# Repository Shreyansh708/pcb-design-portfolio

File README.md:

# PCB Design Portfolio

Electronics PCB design projects developed using KiCad, covering schematic capture, PCB layout, routing, design verification, and manufacturing outputs.

---

## 01 — Single LED PCB

**Status:** Completed  
**EDA Tool:** KiCad 10.0.5  
**Board Type:** 2-layer PCB  
**Board Dimensions:** 25.05 mm × 44.05 mm  
**Board Thickness:** 1.6 mm
### PCB Layout

### Schematic

### Overview

A compact single-LED PCB designed through the complete PCB development workflow, from schematic capture to PCB layout and manufacturing-output generation.

### Design Workflow

- Schematic capture
- Component placement
- PCB layout and routing
- Board outline definition
- Design-rule verification
- Gerber generation
- PTH and NPTH drill-file generation

### Project Files

The repository contains:

- KiCad project file (`.kicad_pro`)
- KiCad schematic (`.kicad_sch`)
- KiCad PCB layout (`.kicad_pcb`)
- Gerber manufacturing files
- PTH and NPTH drill files
- Gerber job file

### Tools

**KiCad 10.0.5**

---

## 02 — AstraDrive BLDC/PMSM Controller

**Status:** Work in Progress  
**EDA Tool:** KiCad  
**Controller:** STM32G474RE  
**System:** 48 V 3-phase BLDC/PMSM motor controller

### Overview

A hardware development project for a 48 V 3-phase BLDC/PMSM motor controller, designed around an STM32G4 microcontroller and intended for applications such as robotics, AGVs, drones, and electric mobility.

The project is being developed as a hierarchical KiCad design with dedicated functional subsystems.

### Current Architecture

The design currently includes:

- STM32G474RE control subsystem
- 3-phase MOSFET bridge
- Gate-driver subsystem
- Current sensing
- Hall-sensor feedback
- Encoder interface
- DC-bus voltage sensing
- Temperature monitoring
- CAN-FD interface
- Display/UI interface
- Programming/debug interface

### Development Status

The system architecture and hierarchical schematic are currently under development. PCB component placement and routing are the next stages of development.

## About

Electrical & Electronics Engineering undergraduate interested in:

- Embedded Systems
- ARM Microcontrollers
- PCB Design
- IoT
- Motor Control
- Digital Electronics
- Hardware Development
- Low-level Firmware
- ---

## 03 — Heart-Shaped Decorative LED PCB

**Status:** Work in Progress — PCB Routing  
**EDA Tool:** KiCad 10.0  
**Board:** 2-layer PCB  
**Thickness:** 1.6 mm

### Overview

A custom heart-shaped LED PCB currently under development. The project explores custom board geometry, component placement, and PCB routing using KiCad.

### Current Development

- Custom heart-shaped board outline
- Component placement
- PCB routing in progress
- Design-rule verification to follow

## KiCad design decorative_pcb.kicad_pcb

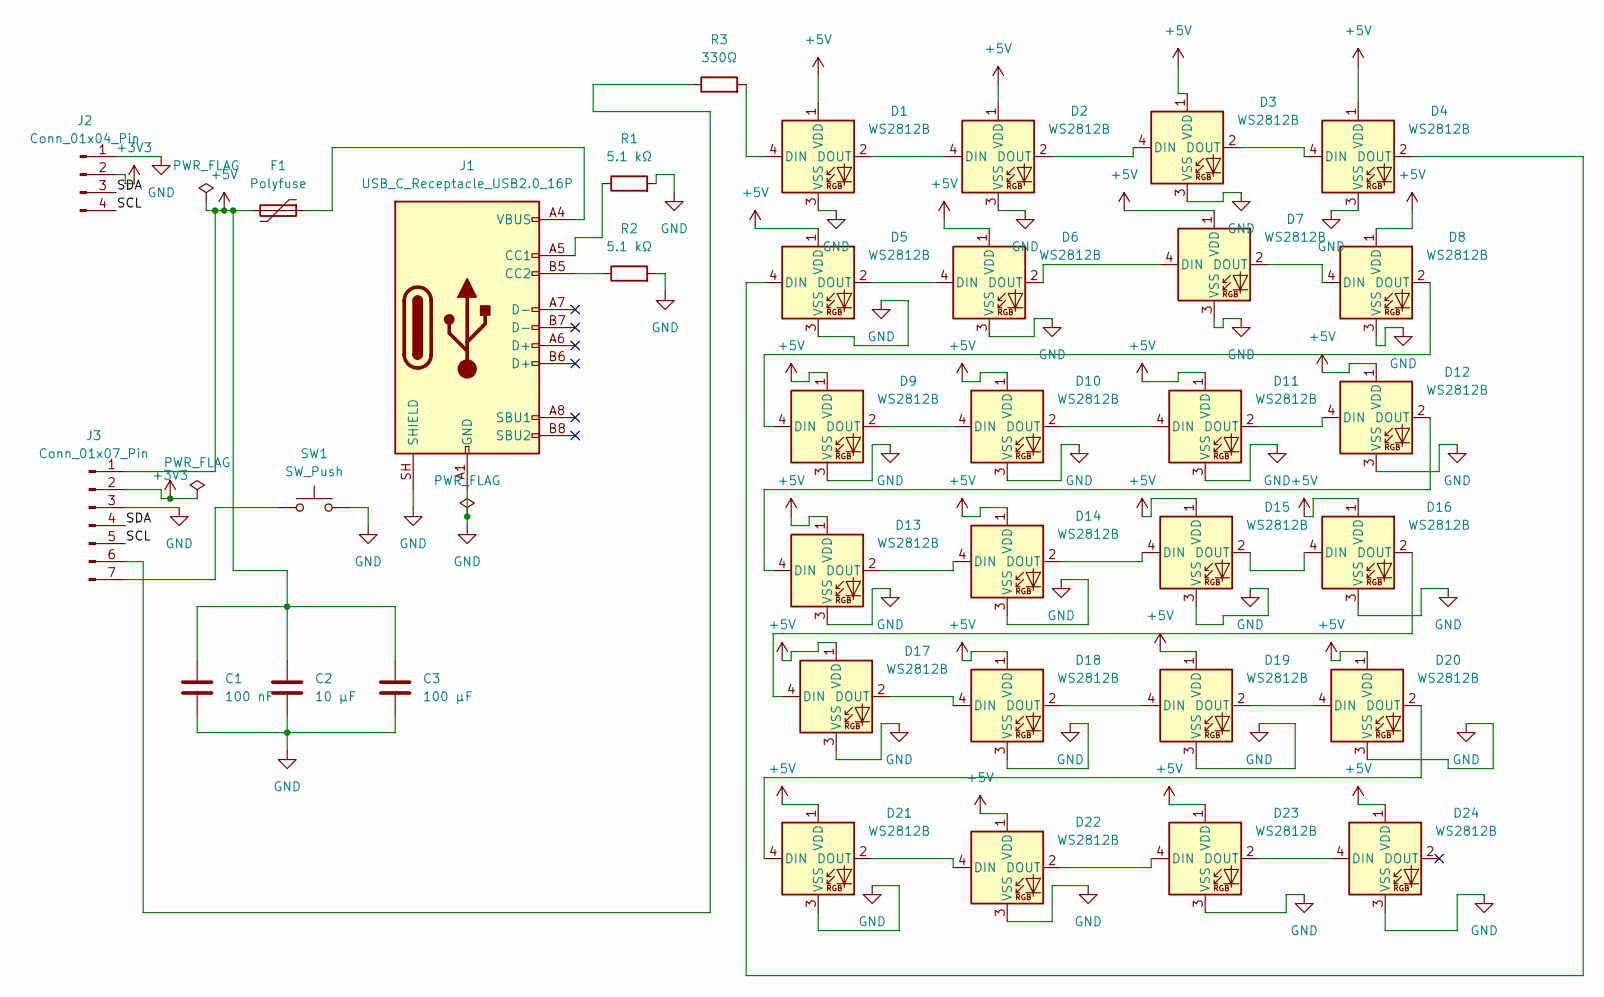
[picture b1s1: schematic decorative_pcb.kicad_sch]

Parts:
C1: 100 nF; C_0805_2012Metric
C2: 10 µF; C_0805_2012Metric
C3: 100 µF; C_Radial_D5.0mm_H5.0mm_P2.00mm
D1, D2, D3, D4, D5, D6, D7, D8, D9, D10, D11, D12, D13, D14, D15, D16, D17, D18, D19, D20, D21, D22, D23, D24: WS2812B; LED_WS2812B_PLCC4_5.0x5.0mm_P3.2mm
F1: Polyfuse; Fuse_Bourns_MF-RG300
J1: USB_C_Receptacle_USB2.0_16P; USB_C_Receptacle_GCT_USB4105-xx-A_16P_TopMnt_Horizontal
J2: Conn_01x04_Pin; FanPinHeader_1x04_P2.54mm_Vertical
J3: Conn_01x07_Pin; PinHeader_1x07_P2.54mm_Vertical
R1, R2: 5.1 kΩ; R_0805_2012Metric
R3: 330Ω; R_0805_2012Metric
SW1: SW_Push; SW_PUSH_6mm

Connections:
+3V3: J2.2, J3.2
+5V: C1.1, C2.1, C3.1, D1.1 (VDD), D2.1 (VDD), D3.1 (VDD), D4.1 (VDD), D5.1 (VDD), D6.1 (VDD), D7.1 (VDD), D8.1 (VDD), D9.1 (VDD), D10.1 (VDD), D11.1 (VDD), D12.1 (VDD), D13.1 (VDD), D14.1 (VDD), D15.1 (VDD), D16.1 (VDD), D17.1 (VDD), D18.1 (VDD), D19.1 (VDD), D20.1 (VDD), D21.1 (VDD), D22.1 (VDD), D23.1 (VDD), D24.1 (VDD), F1.2, J3.1
/SCL: J2.4, J3.5
/SDA: J2.3, J3.4
GND: C1.2, C2.2, C3.2, D1.3 (VSS), D2.3 (VSS), D3.3 (VSS), D4.3 (VSS), D5.3 (VSS), D6.3 (VSS), D7.3 (VSS), D8.3 (VSS), D9.3 (VSS), D10.3 (VSS), D11.3 (VSS), D12.3 (VSS), D13.3 (VSS), D14.3 (VSS), D15.3 (VSS), D16.3 (VSS), D17.3 (VSS), D18.3 (VSS), D19.3 (VSS), D20.3 (VSS), D21.3 (VSS), D22.3 (VSS), D23.3 (VSS), D24.3 (VSS), J1.A1 (GND), J1.A12 (GND), J1.B1 (GND), J1.B12 (GND), J1.SH (SHIELD), J2.1, J3.3, R1.2, R2.2, SW1.2
unnamed: D1.4 (DIN), R3.2
unnamed: D1.2 (DOUT), D2.4 (DIN)
unnamed: D2.2 (DOUT), D3.4 (DIN)
unnamed: D3.2 (DOUT), D4.4 (DIN)
unnamed: D4.2 (DOUT), D5.4 (DIN)
unnamed: D5.2 (DOUT), D6.4 (DIN)
unnamed: D6.2 (DOUT), D7.4 (DIN)
unnamed: D7.2 (DOUT), D8.4 (DIN)
unnamed: D8.2 (DOUT), D9.4 (DIN)
unnamed: D9.2 (DOUT), D10.4 (DIN)
unnamed: D10.2 (DOUT), D11.4 (DIN)
unnamed: D11.2 (DOUT), D12.4 (DIN)
unnamed: D12.2 (DOUT), D13.4 (DIN)
unnamed: D13.2 (DOUT), D14.4 (DIN)
unnamed: D14.2 (DOUT), D15.4 (DIN)
unnamed: D15.2 (DOUT), D16.4 (DIN)
unnamed: D16.2 (DOUT), D17.4 (DIN)
unnamed: D17.2 (DOUT), D18.4 (DIN)
unnamed: D18.2 (DOUT), D19.4 (DIN)
unnamed: D19.2 (DOUT), D20.4 (DIN)
unnamed: D20.2 (DOUT), D21.4 (DIN)
unnamed: D21.2 (DOUT), D22.4 (DIN)
unnamed: D22.2 (DOUT), D23.4 (DIN)
unnamed: D23.2 (DOUT), D24.4 (DIN)
unnamed: F1.1, J1.A4 (VBUS), J1.A9 (VBUS), J1.B4 (VBUS), J1.B9 (VBUS)
unnamed: J1.A5 (CC1), R1.1
unnamed: J1.B5 (CC2), R2.1
unnamed: J3.6, R3.1
unnamed: J3.7, SW1.1

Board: 2 copper layers, 35 parts (0 on the bottom side), 34 nets, no tracks yet.

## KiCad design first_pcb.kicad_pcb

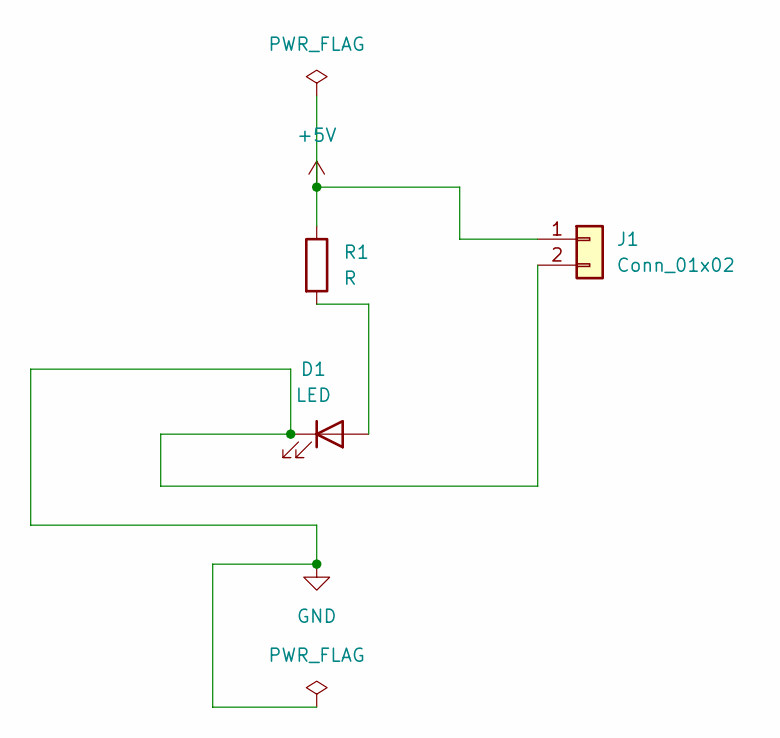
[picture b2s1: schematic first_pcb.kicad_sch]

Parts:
D1: LED; LED_D5.0mm
J1: Conn_01x02; PinHeader_1x02_P2.54mm_Vertical
R1: R; R_Axial_DIN0207_L6.3mm_D2.5mm_P7.62mm_Horizontal

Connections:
+5V: J1.1, R1.1
GND: D1.1 (K), J1.2
unnamed: D1.2 (A), R1.2

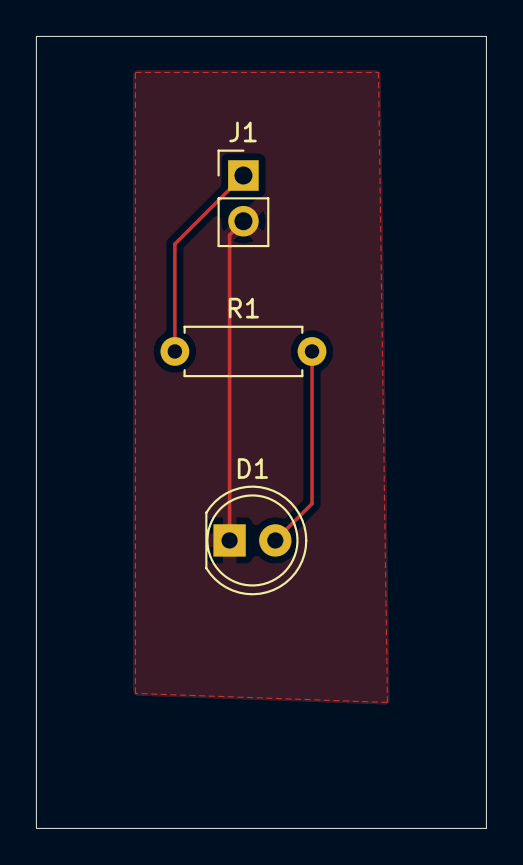
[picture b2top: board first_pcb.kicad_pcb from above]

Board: 2 copper layers, 25.0 x 44.0 mm, 3 parts (0 on the bottom side), 3 nets.
